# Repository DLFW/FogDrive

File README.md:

Welcome to FogDrive
===================

The FogDrive project aims to provide free and open source electronics for vaping devices, the so called “mods”.
This includes the circuit specifications, parts lists, proposals on how to build the actual board
and – last but not least – the firmware for the micro-controller which is part of the circuit.

FogDrive is a free and open project, published under the [GNU General Public License](http://www.gnu.org/licenses/), version 3. We have no commercial interests and provide only information on how to build the electronics on your own.

FogDrive is under very early development. Mira is the first simple FogDrive that just switches the vaporizer on and off via a MOSFET.
The vaporizer is driven directly by the battery. In addition, Mira supports a few tiny comfort
features like battery voltage supervision. The next circuit is in an early planning phase.

Mira is currently in beta status and we are working on an online documentation and the host the the FogDrive builts.

For all of those out there who are interested to participate in the development: you are very welcome! Especially people who can contribute to the design of the voltage converters and electronic geeks in general could fill a significant gap. :) If you’re interested, please mail to `fogdrive {ät} llin -fullstop- info` or leave a message on the GitHub wiki.

* * *

FogDrive is a free and open project, you can redistribute it and/or modify
it under the terms of the [GNU General Public License](http://www.gnu.org/licenses/) as published by
the Free Software Foundation, either version 3 of the License, or any later version.

FogDrive is distributed in the hope that it will be useful,
but without any warranty; without even the implied warranty of
merchantability or fitness for a particular purpose.  See the
GNU General Public License for more details.

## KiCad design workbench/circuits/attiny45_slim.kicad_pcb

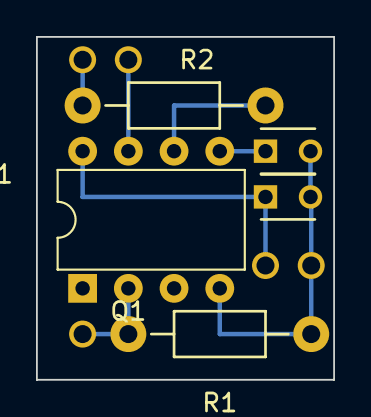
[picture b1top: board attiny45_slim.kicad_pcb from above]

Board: 2 copper layers, 16.5 x 19.1 mm, 7 parts (0 on the bottom side), 5 nets.

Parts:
Bat+: SolderWirePad_single_0-8mmDrill
C1, C2: 10nF; C_Disc_D3_P2.5
IC1: ATTINY45-P; DIP-8_W7.62mm
Q1: RLB3034; WireConnection_1.50mmDrill
R1: 22kΩ; Resistor_Horizontal_RM10mm
R2: 100Ω; Resistor_Horizontal_RM10mm

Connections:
+BATT: Bat+.1, C1.1, IC1.8
/Mira/AREF: C2.1, IC1.5
/Mira/FIRE: IC1.2, Q1.2, R1.1
/Mira/LED: IC1.6, R2.2
GND: C1.2, C2.2, IC1.4, R1.2

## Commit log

2016-09-29 Added a fresh Sphinx document and the first logo. ;)
2016-09-30 Wrote a first intro text for the doc and added a simple backlog for the first significant steps. The logo is added as png file which will be removed later when the build chain is set up properly sinc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
2016-11-28 Updated license file, the documentation index and the readme file. The readme file mostly copies the documentation index. If they will continue to share their content, it might be feasable to generat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
2016-12-05 Added the first fogdrive sources from a private SVN repo.
    The first FogDrive, Mira, is under development.
    So far, it has a debounced switch which is directly used to activate/decative the vaporizer.
    The basic architecture ideas are in place and the preconditions of building it for multiple
    architecture should also be there. The build system is set up with SCons. A simple framework
    for variant management is implemented.
    The main focus now is on battery voltage measurement, a more sophisticated LED control and
2016-12-05 * Implemented very rough battery voltage measurement * Enhanced deviface a little (removed info method, added a put method for uint16)
2016-12-09 Did a little refactoring and started with a PWM control for the LED(s). It doesn't really work at the moment. The LED flicers and the brigthness value has a very unexpected effect. What I will do nex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
2016-12-12 Refactoring UI timer
    Changed the timer used for the 10ms ISR to timer 2. Deactivated the old LED PWM approach.
    Furthermore I added a 8MHz variant of Mira in the SConstruct.
2016-12-13 HW PWM Experiment A HW PWM is working (T0A). It is just demonstarted by cyclically increasing the brightness. A first deviface command has been introduce to force the brightness.
2016-12-16 LED control
    LED control is under development. The basic HE PWM and the modularization of the LED logic work.
    Some small refactorings.
2016-12-16 LED modularization
    Moved initialization of LED PWM stuff into led module. Little cleanup.
2016-12-17 LED PWM changed to inverted mode The HW PWM for the LED is changed to inverted mode go be able to get the LED fully off.
2016-12-17 Button logic module added Added a basic button module which detects press, release and multi-click events. It's not integrated into the UI so far.
2016-12-17 Button logic for fireing Integrated the button logic into the UI: The fire is switched on now when the button is pressed, but not clicked
2016-12-18 Tiny typo
2016-12-18 Started to implement a smart LED control
2016-12-19 Enhanced LED dimming (better value table) and added LED debug command
2016-12-19 Enhanced LED control
    The LED module was enhanced to be able to "play" small "light programs".
2016-12-19 LED control: fix and application
    Fixed an error in the linear dim command, used the first programs in the ui module.
    The linear dim function doesn't work well. Dimming down doesn't work at all and dimming up hasn't a good value sequence.
2016-12-20 LED control fix
    Fixed the linear dim command of the led module, added a UART put method for int8_t
2016-12-20 Battery voltage measurement: added smoothing
    The voltage measurement for the battery takes four separate measurements now, throws the lowest and the highest value and calculates the avverage for the two median values.
2016-12-21 Integrated battery voltage into UI, Code-Cleanup
    The battery voltage measurement is triggered cyclically now.
    The UI lights up the LED now when the voltage drops below a magic value (3,4 V).
    Added some deviface commands.
2016-12-22 Declared a few variables static
    Declared the local variables of the UI and the logic module as static to avoid global linkage conflicts.
2016-12-25 Added first circuit schematics
2017-01-01 Added first schematic artifacts for the tiny 45 port of Mira.
2017-01-05 Removed MCU dependency from hardware module
    and a little code cleanup
2017-01-05 added a 2nd stage of battery voltage warning (blinking for very low voltage)
2017-01-06 Reworked the build setup to support multiple MCUs for a FogDrive.
2017-01-06 Ported Mira to Tiny45... ...but the binary is too big for the tiny's flash and untested. So, the built hex file is not usable at the moment.
2017-01-06 Reduced flash size of Mira for the Tiny The needed size of flash memory was reduced by excluding deviface (UART) related code by the preprocessor. The preprocessor checks wether "UART_ENABLED" is def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
2017-01-06 Various fixes, Tiny45 port done * Fixed a bug of the atmega328p module, introduced while doing the Tiny port * Fixed a bug in the attiny45 module (wrong PWM channel) * Fixed a deviface command: strin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
2017-01-06 Fixed a bug in the LED module and fine tuned the UI output
2017-01-08 Added display of battery voltage (last load measurement) on double click
2017-01-15 added PCB laybout for Mira with AT Tiny 45
2017-01-15 Simple implementation of power down works for the Mega328
2017-01-15 Power down feature in progress Moved power down responsibility to logic module. Added proper down methods for the UI and the hardware modules. Added clear function for queues.
2017-01-21 Implemented first working version of switching-on-off feature. The switch-off action doesn't have a working led program (aborted by the UIs power off function). Also started with a very few lines of 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
2017-01-21 Switch-on-off feature implemented for the Tiny45, reactivated build for Tiny45. Also changed some UI behavior (LED programs) to save some program memory. It's very tight for the Tiny45 now.
2017-01-22 Added some simple button graphics for the docs.
2017-01-22 Moved artwork area to the workbench directory.
2017-01-29 Cleaned up the Mira KiCad files... ... and moved them to an approproate subdirectory. Added the Mira "slim" PCB. Removed an old Sphinx page and moved the Sphinx project logo.
2017-01-29 Integrated the Sphinx documentation into the SCons build
2017-01-29 Sphinx documentation enhanced.
2017-01-29 *.png to gitignore in the logos directory
2017-01-30 Some small documentation enhancements
2017-01-31 Updated README.md (current status)
2017-01-31 Small doc updates
2017-02-18 Made config of the Sphinx documentation more portable
2017-02-19 Enhanced LED programs and flash footprint a bit
2017-02-19 Added callback command to the LED module, implemented proper LED programs for switching on and off
2017-02-19 Added auto-switch-off on very low battery voltage (2.9V) with LED blinking
2017-02-23 added a little bit more content for the dev page
2017-02-23 Added timeout feature for the button module
2017-02-23 Reducing flash footprint in progress (voltage measurement currently broken!)
2017-02-23 Fixed a tiny bug that disabled the deviface
2017-02-23 Voltage measurement works again with smaller flash footprint (removed median calculation - but that doesn't harm the measurement)
2017-02-23 Removed deprecated stuff of the removed unstressed voltage measurement
2017-02-23 UI rework: on/off by 3-click, on-indicator on 1-click, reaction on timeout, LED dim-up on button release after timeout
